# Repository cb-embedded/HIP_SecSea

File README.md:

# HIP_SecSea
Hack In Provence badge for SecSea

## Changes from V1.1 (@chris_cannes)

This version is based on the V1.1 design by @chris_cannes. The following changes were made:

**Antenna area**
- Antenna placement and copper zones reworked to comply with CC1101 datasheet requirements.
- Replaced four independent copper cutout polygons with a proper keepout zone (larger, as required by the doc).

**Layer stackup**
- Added a dedicated Ground plane (inner layer).
- Added a dedicated 3.3V Power plane (inner layer).
- Main routing moved to Top and Bottom layers.

**Power distribution**
- The 3.3V distribution tree replaced by a solid 3.3V power plane.

**GND stitching**
- Stitching vias replaced by GND vias placed as close as possible to GND pads, connecting directly into the ground plane. This ensures a controlled, low-impedance GND return path.

## TODO (before production)

- [X] Rebuild copper planes and stitching vias: add back a proper grid of stitching vias (perimeter, around RF keepout zone, under CC1101) in addition to the pad-level GND vias.
- [X] **Replace C21 and C26 — 220pF X7R on RF path**: TI reference design specifies NP0/C0G for these positions. Replace with Murata [`GRM1555C1H221JA01D`](https://www.lcsc.com/product-detail/C71693.html) (C0G, 220pF, 50V, 0402, LCSC C71693). Current part [`0402B221K500NT`](https://www.lcsc.com/product-detail/C1530.html) (FH, LCSC C1530, X7R) deviates from reference design; do not second-guess NP0 in an RF path.
- [X] **Verify crystal load capacitors C17, C18 (27pF)**: X2 specifies 15pF load. CC1101 datasheet gives Cparasitic ≈ 2.5pF typical. Effective load = 27/2 + 2.5 = 16pF — 1pF above target, acceptable. Current 27pF value is correct; no change needed unless crystal frequency trim is required.

- [ ] Use tented vias;
- [X] On ne le fait plus (trop long) ~~TODO: Changer pour antenne 868MHz (Meilleure efficacité vs petite taille de PCB), (si simple à changer).~~
- [ ] Prod entre 5 et 10.

## Production Preview JLCPCB

See [JLCPCB Pictures in this folder](KiCad_src_V1_2/production_preview)

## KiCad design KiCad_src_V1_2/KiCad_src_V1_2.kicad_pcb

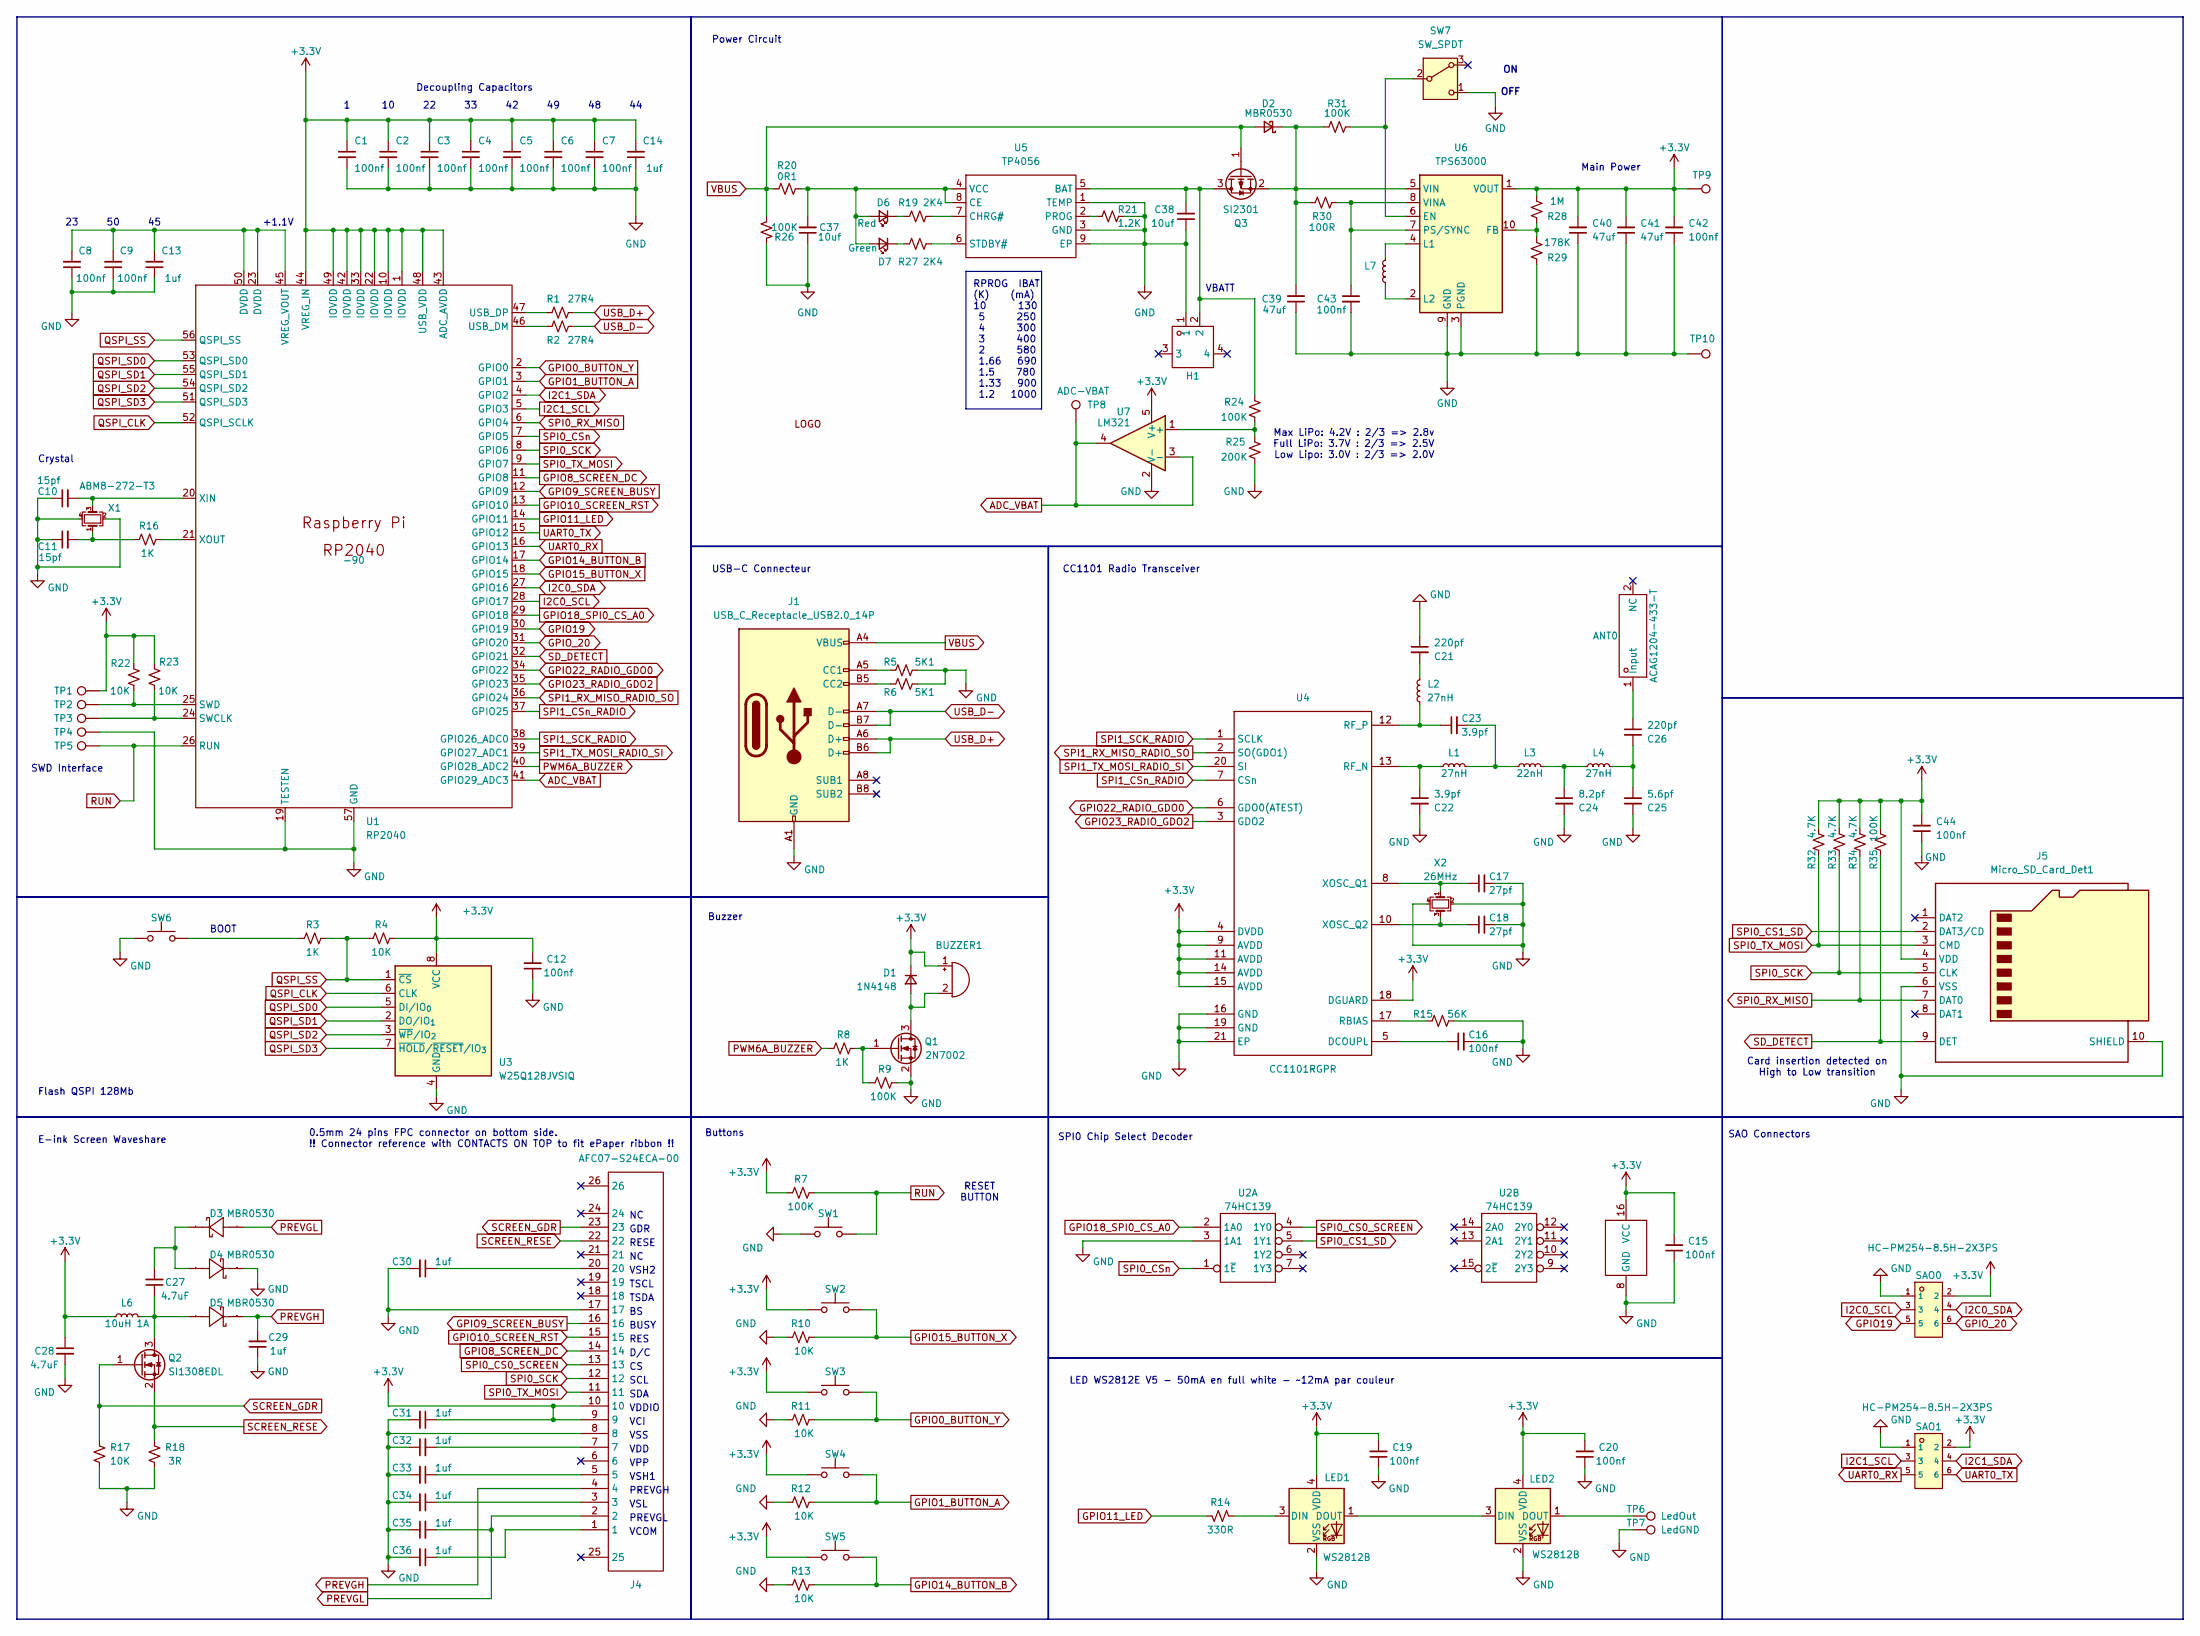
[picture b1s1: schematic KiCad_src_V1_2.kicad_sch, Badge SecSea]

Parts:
ANT0: ACAG1204-433-T; ANT-SMD_L12.0-W4.0_ACAG1204-915-T; Manufacturer Part ACAG1204-433-T; LCSC Part # C6113830
BUZZER1: MLT-8530; Buzzer MLT-8530; Manufacturer Part MLT-8530; LCSC Part # C94599
C1, C2, C3, C4, C5, C6, C7, C8, C9, C12, C15, C16, C19, C20, C42, C43, C44: 100nf; C_0402_1005Metric; Manufacturer Part CL05B104KO5NNNC; LCSC Part # C1525
C10, C11: 15pf; C_0402_1005Metric; Manufacturer Part 0402CG150J500NT; LCSC Part # C1548
C13, C14: 1uf; C_0402_1005Metric; Manufacturer Part CL05A105KA5NQNC; LCSC Part # C52923
C17, C18: 27pf; C_0402_1005Metric; Manufacturer Part 0402CG270J500NT; LCSC Part # C1557
C21, C26: 220pf; C_0402_1005Metric; Manufacturer Part 0402B221K500NT; LCSC Part # C1530
C22, C23: 3.9pf; C_0402_1005Metric; Manufacturer Part CC0402BRNPO9BN3R9; LCSC Part # C505474
C24: 8.2pf; C_0402_1005Metric; Manufacturer Part 0402CG8R2C500NT; LCSC Part # C1579
C25: 5.6pf; C_0402_1005Metric; Manufacturer Part GRM1555C1H5R6BA01D; LCSC Part # C76976
C27, C28: 4.7uF; C_0805_2012Metric; Manufacturer Part CL21A475KAQNNNE; LCSC Part # C1779
C29, C30, C31, C32, C33, C34, C35, C36: 1uf; C_0805_2012Metric; Manufacturer Part CL21B105KBFNNNE; LCSC Part # C28323
C37, C38: 10uf; C_0805_2012Metric; Manufacturer Part CL21A106KAYNNNE; LCSC Part # C15850
C39, C40, C41: 47uf; C_0805_2012Metric; Manufacturer Part CL21A476MQYNNNE; LCSC Part # C16780
D1: 1N4148; D_SOD-123; Manufacturer Part 1N4148W; LCSC Part # C81598
D2, D3, D4, D5: MBR0530; D_SOD-123; Manufacturer Part MBR0530; LCSC Part # C5204746
D6: Red; LED_0603_1608Metric; Manufacturer Part XL-1608SURC-06; LCSC Part # C965799
D7: Green; LED_0603_1608Metric; Manufacturer Part XL-1608UGC-04; LCSC Part # C965804
G1: LOGO; silkscreen_cigale
H1: WAFER-PH2.0-2PWB; CONN-SMD_2P-P2.00_XUNPU_WAFER-PH2.0-2PWB; Manufacturer Part WAFER-PH2.0-2PWB; LCSC Part # C3029440
J1: USB_C_Receptacle_USB2.0_14P; USB-C_C165948; Manufacturer Part TYPE-C-31-M-12; LCSC Part # C165948
J4: AFC07-S24ECA-00; FPC_24; Manufacturer Part AFC07-S24ECA-00; LCSC Part # C262643
J5: Micro_SD_Card_Det1; MicroSD TF-115-BCP9; Manufacturer Part XUNPU TF-115-BCP9; LCSC Part # C720505
L1, L2, L4: 27nH; L_0402_1005Metric; Manufacturer Part LQG15HS27NJ02D; LCSC Part # C12669
L3: 22nH; L_0402_1005Metric; Manufacturer Part SDCL1005C22NJTDF; LCSC Part # C15178
L6: 10uH 1A; L_Ferrocore_DLG-0403; Manufacturer Part CY43-10UH; LCSC Part # C2929419
L7: 2.2µH; L_APV_ANR4012; Manufacturer Part NR4018S2R2MT; LCSC Part # C28642347
LED1, LED2: WS2812B; LED_WS2812B-2020_PLCC4_2.0x2.0mm; Manufacturer Part WS2812B-2020; LCSC Part # C965555
Q1: 2N7002; SOT-23; Manufacturer Part 2N7002; LCSC Part # C8545
Q2: SI1308EDL; SOT-323_SC-70; Manufacturer Part SI1308EDL; LCSC Part # C7603347
Q3: SI2301; SOT-23; Manufacturer Part SI2301; LCSC Part # C2891731
R1, R2: 27R4; R_0402_1005Metric; Manufacturer Part RC-02W27R4FT; LCSC Part # C321420
R3, R8, R16: 1K; R_0402_1005Metric; Manufacturer Part 0402WGF1001TCE; LCSC Part # C11702
R4, R10, R11, R12, R13, R17, R22, R23: 10K; R_0402_1005Metric; Manufacturer Part 0402WGF1002TCE; LCSC Part # C25744
R5, R6: 5K1; R_0402_1005Metric; Manufacturer Part 0402WGF5101TCE; LCSC Part # C25905
R7, R9, R24, R26, R31, R35: 100K; R_0402_1005Metric; Manufacturer Part 0402WGF1003TCE; LCSC Part # C25741
R14: 330R; R_0402_1005Metric; Manufacturer Part 0402WGF3300TCE; LCSC Part # C25104
R15: 56K; R_0402_1005Metric; Manufacturer Part 0402WGF5602TCE; LCSC Part # C25796
R18: 3R; R_0402_1005Metric; Manufacturer Part FRC0402F3R00TS; LCSC Part # C2933093
R19, R27: 2K4; R_0402_1005Metric; Manufacturer Part 0402WGF2401TCE; LCSC Part # C25882
R20: 0R1; R_1206_3216Metric; Manufacturer Part 1206W4F100LT5E; LCSC Part # C25334
R21: 1.2K; R_0805_2012Metric_Pad1.20x1.40mm_HandSolder; Manufacturer Part 0805W8F1201T5E; LCSC Part # C17379
R25: 200K; R_0402_1005Metric; Manufacturer Part 0402WGF2003TCE; LCSC Part # C25764
R28: 1M; R_0402_1005Metric; Manufacturer Part FRC0402F1004TS; LCSC Part # C2909328
R29: 178K; R_0402_1005Metric; Manufacturer Part FRC0402F1783TS; LCSC Part # C3013156
R30: 100R; R_0402_1005Metric; Manufacturer Part FRC0402J101TS; LCSC Part # C2906884
R32, R33, R34: 4.7K; R_0402_1005Metric; Manufacturer Part FRC0402J472 TS; LCSC Part # C2906941
SAO0, SAO1: HC-PM254-8.5H-2X3PS; C22373944_HDR-SMD_6P-P2_54-V-F-R2-C3-LS7_1; LCSC C22373944
SW1, SW6: TS-1187A-B-A-B; SW_Push_1P1T_XKB_TS-1187A; Manufacturer Part TS-1187A-B-A-B; LCSC Part # C318884
SW2, SW3: K2-1112SW-A4SW-04; Manufacturer Part K2-1112SW-A4SW-04; LCSC Part # C223811
SW4, SW5: XDTD-6650; SW_Push_1P1T_NO_E-Switch_TL3301NxxxxxG; Manufacturer Part XDTD-6643-L01; LCSC Part # C7498208
SW7: SW_SPDT; SPDT SMD slide switch; Manufacturer Part SSSS811101; LCSC Part # C109335
TP1, TP2, TP3, TP4, TP5: TestPoint; TestPoint_Pad_D1.5mm
TP6: LedOut; TestPoint_Pad_D1.5mm
TP7: LedGND; TestPoint_Pad_D1.5mm
TP8, TP9, TP10: ADC-VBAT; TestPoint_Pad_D1.5mm
U1: RP2040; QFN-56-1EP_7x7mm_P0.4mm_EP3.2x3.2mm; Manufacturer Part RP2040; LCSC Part # C2040
U2: 74HC139; SOIC-16_3.9x9.9mm_P1.27mm; Manufacturer Part 74HC139D,653; LCSC Part # C5603
U3: W25Q128JVSIQ; SOIC-8_5.3x5.3mm_P1.27mm; Manufacturer Part W25Q128JVSIQ; LCSC Part # C97521
U4: CC1101RGPR; QFN-20-1EP_L4.0-W4.0-P0.5-EP2.4; Manufacturer Part CC1101RGPR; LCSC Part # C29953
U5: TP4056; ESOP-8_L4.9-W3.9-P1.27-LS6.0-BL-EP; Manufacturer Part TP4056; LCSC Part # C725790
U6: TPS63000; Texas_DRC0010J; Manufacturer Part TPS63000DRCR; LCSC Part # C24966
U7: LM321; SOT-23-5; Manufacturer Part LM321H-TR; LCSC Part # C2927688
X1: ABM8-272-T3; Crystal_SMD_Abracon_ABM8AIG-4Pin_3.2x2.5mm; Manufacturer Part ABM8-272-T3; LCSC Part # C20625731
X2: 26MHz; Crystal_SMD_3225-4Pin_3.2x2.5mm; Manufacturer Part S3226000151040; LCSC Part # C479205

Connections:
+3.3V: BUZZER1.1 (+), C1.1, C2.1, C3.1, C4.1, C5.1, C6.1, C7.1, C12.2, C14.2, C15.2, C19.2, C20.2, C28.1, C31.1, C40.2, C41.2, C42.2, C44.2, D1.1 (K), J4.9, J4.10, J5.4 (VDD), L6.1, LED1.4 (VDD), LED2.4 (VDD), R4.2, R7.1, R22.2, R23.2, R28.1, R32.2, R33.2, R34.2, R35.2, SAO0.2, SAO1.2, SW2.1, SW3.2, SW4.2, SW5.2, TP1.1 (1_1), TP9.1 (1_1), U1.1 (IOVDD), U1.10 (IOVDD), U1.22 (IOVDD), U1.33 (IOVDD), U1.42 (IOVDD), U1.43 (ADC_AVDD), U1.44 (VREG_IN), U1.48 (USB_VDD), U1.49 (IOVDD), U2.16 (VCC), U3.8 (VCC), U4.4 (DVDD), U4.9 (AVDD), U4.11 (AVDD), U4.14 (AVDD), U4.15 (AVDD), U4.18 (DGUARD), U6.1 (VOUT), U7.5 (V+)
ADC_VBAT: TP8.1 (1_1), U1.41 (GPIO29_ADC3), U7.3 (-), U7.4
GND: C1.2, C2.2, C3.2, C4.2, C5.2, C6.2, C7.2, C8.1, C9.1, C10.1, C11.1, C12.1, C13.1, C14.1, C15.1, C16.2, C17.2, C18.2, C19.1, C20.1, C21.1, C22.2, C24.2, C25.2, C28.2, C29.1, C30.2, C31.2, C32.1, C33.2, C34.2, C35.1, C36.2, C37.1, C38.1, C39.1, C40.1, C41.1, C42.1, C43.2, C44.1, D4.1 (K), H1.1, J1.A1 (GND), J1.B1 (GND), J4.8, J4.17, J5.6 (VSS), J5.10 (SHIELD), LED1.2 (VSS), LED2.2 (VSS), Q1.2 (S), R5.1, R6.2, R9.2, R10.1, R11.1, R12.1, R13.1, R15.2, R17.1, R18.1, R21.1, R25.1, R26.2, R29.2, SAO0.1, SAO1.1, SW1.1, SW6.1, SW7.1 (C), TP4.1 (1_1), TP7.1 (1_1), TP10.1 (1_1), U1.19 (TESTEN), U1.57 (GND), U2.3 (1A1), U2.8 (GND), U3.4 (GND), U4.16 (GND), U4.19 (GND), U4.21 (EP), U5.1 (TEMP), U5.3 (GND), U5.9 (EP), U6.3 (PGND), U6.9 (GND), U6.11 (PGND), U7.2 (V-), X1.2, X1.4, X2.2, X2.4
GPIO0_BUTTON_Y: R11.2, SW3.1, U1.2 (GPIO0)
GPIO1_BUTTON_A: R12.2, SW4.1, U1.3 (GPIO1)
GPIO8_SCREEN_DC: J4.14, U1.11 (GPIO8)
GPIO9_SCREEN_BUSY: J4.16, U1.12 (GPIO9)
GPIO10_SCREEN_RST: J4.15, U1.13 (GPIO10)
GPIO11_LED: R14.1, U1.14 (GPIO11)
GPIO14_BUTTON_B: R13.2, SW5.1, U1.17 (GPIO14)
GPIO15_BUTTON_X: R10.2, SW2.2, U1.18 (GPIO15)
GPIO18_SPI0_CS_A0: U1.29 (GPIO18), U2.2 (1A0)
GPIO19: SAO0.5, U1.30 (GPIO19)
GPIO22_RADIO_GDO0: U1.34 (GPIO22), U4.6 (GDO0(ATEST))
GPIO23_RADIO_GDO2: U1.35 (GPIO23), U4.3 (GDO2)
GPIO_20: SAO0.6, U1.31 (GPIO20)
I2C0_SCL: SAO0.3, U1.28 (GPIO17)
I2C0_SDA: SAO0.4, U1.27 (GPIO16)
I2C1_SCL: SAO1.3, U1.5 (GPIO3)
I2C1_SDA: SAO1.4, U1.4 (GPIO2)
unnamed: ANT0.1 (Input_1), C26.1
unnamed: BUZZER1.2 (-), D1.2 (A), Q1.3 (D)
unnamed: C11.2, R16.1, X1.1
unnamed: C21.2, L2.2
unnamed: C23.2, L1.2, L3.1
unnamed: C24.1, L3.2, L4.1
unnamed: C25.1, C26.2, L4.2
unnamed: C30.1, J4.20
unnamed: C32.2, J4.7
unnamed: C33.1, J4.5
unnamed: C34.1, J4.3
unnamed: C36.1, J4.1
unnamed: C39.2, D2.1 (K), Q3.2 (S), R30.2, R31.1, U6.5 (VIN)
unnamed: C27.2, D3.1 (K), D4.2 (A)
unnamed: C27.1, D5.2 (A), L6.2, Q2.3 (D)
unnamed: C37.2, D6.2 (A), D7.2 (A), R20.1, U5.4 (VCC), U5.8 (CE)
unnamed: D6.1 (K), R19.2
unnamed: D7.1 (K), R27.2
unnamed: J1.A5 (CC1), R5.2
unnamed: J1.B5 (CC2), R6.1
unnamed: LED1.3 (DIN), R14.2
unnamed: LED1.1 (DOUT), LED2.3 (DIN)
unnamed: LED2.1 (DOUT), TP6.1 (1_1)
unnamed: Q1.1 (G), R8.2, R9.1
unnamed: C38.2, H1.2, Q3.3 (D), R24.2, U5.5 (BAT)
unnamed: R3.2, SW6.2
unnamed: R31.2, SW7.2 (B), U6.6 (EN)
unnamed: R23.1, TP3.1 (1_1), U1.24 (SWCLK)
unnamed: R22.1, TP2.1 (1_1), U1.25 (SWD)
unnamed: R2.1, U1.46 (USB_DM)
unnamed: R1.2, U1.47 (USB_DP)
unnamed: C8.2, C9.2, C13.2, U1.23 (DVDD), U1.45 (VREG_VOUT), U1.50 (DVDD)
unnamed: C10.2, U1.20 (XIN), X1.3
unnamed: R16.2, U1.21 (XOUT)
unnamed: C16.1, U4.5 (DCOUPL)
unnamed: R15.1, U4.17 (RBIAS)
unnamed: C22.1, L1.1, U4.13 (RF_N)
unnamed: C23.1, L2.1, U4.12 (RF_P)
unnamed: C17.1, U4.8 (XOSC_Q1), X2.1
unnamed: C18.1, U4.10 (XOSC_Q2), X2.3
unnamed: R19.1, U5.7 (CHRG#)
unnamed: R21.2, U5.2 (PROG)
unnamed: R27.1, U5.6 (STDBY#)
unnamed: R28.2, R29.1, U6.10 (FB)
unnamed: L7.2, U6.4 (L1)
unnamed: L7.1, U6.2 (L2)
unnamed: C43.1, R30.1, U6.7 (PS/SYNC), U6.8 (VINA)
unnamed: R24.1, R25.2, U7.1 (+)
PREVGH: C29.2, D5.1 (K), J4.4
PREVGL: C35.2, D3.2 (A), J4.2
PWM6A_BUZZER: R8.1, U1.40 (GPIO28_ADC2)
QSPI_CLK: U1.52 (QSPI_SCLK), U3.6 (CLK)
QSPI_SD0: U1.53 (QSPI_SD0), U3.5 (DI/IO_{0})
QSPI_SD1: U1.55 (QSPI_SD1), U3.2 (DO/IO_{1})
QSPI_SD2: U1.54 (QSPI_SD2), U3.3 (~WP/IO_{2})
QSPI_SD3: U1.51 (QSPI_SD3), U3.7 (~HOLD/~RESET/IO_{3})
QSPI_SS: R3.1, R4.1, U1.56 (QSPI_SS), U3.1 (~CS)
RUN: R7.2, SW1.2, TP5.1 (1_1), U1.26 (RUN)
SCREEN_GDR: J4.23, Q2.1 (G), R17.2
SCREEN_RESE: J4.22, Q2.2 (S), R18.2
SD_DETECT: J5.9 (DET), R35.1, U1.32 (GPIO21)
SPI0_CS0_SCREEN: J4.13, U2.4 (1Y0)
SPI0_CS1_SD: J5.2 (DAT3/CD), U2.5 (1Y1)
SPI0_CSn: U1.7 (GPIO5), U2.1 (1~E)
SPI0_RX_MISO: J5.7 (DAT0), R34.1, U1.6 (GPIO4)
SPI0_SCK: J4.12, J5.5 (CLK), R33.1, U1.8 (GPIO6)
SPI0_TX_MOSI: J4.11, J5.3 (CMD), R32.1, U1.9 (GPIO7)
SPI1_CSn_RADIO: U1.37 (GPIO25), U4.7 (CSn)
SPI1_RX_MISO_RADIO_SO: U1.36 (GPIO24), U4.2 (SO(GDO1))
SPI1_SCK_RADIO: U1.38 (GPIO26_ADC0), U4.1 (SCLK)
SPI1_TX_MOSI_RADIO_SI: U1.39 (GPIO27_ADC1), U4.20 (SI)
UART0_RX: SAO1.5, U1.16 (GPIO13)
UART0_TX: SAO1.6, U1.15 (GPIO12)
USB_D+: J1.A6 (D+), J1.B6 (D+), R1.1
USB_D-: J1.A7 (D-), J1.B7 (D-), R2.2
VBUS: D2.2 (A), J1.A4 (VBUS), J1.B4 (VBUS), Q3.1 (G), R20.2, R26.1

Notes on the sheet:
VDD
VDDIO
E-ink Screen Waveshare
Main Power
RPROG IBAT (K) (mA) 10 130 5 250 4 300 3 400 2 580 1.66 690 1.5 780 1.33 900 1.2 1000
SAO Connectors
VSH1
VPP
TSCL
Flash QSPI 128Mb
VCOM
PREVGH
SDA
VSH2
Max LiPo: 4.2V : 2/3 => 2.8v Full LiPo: 3.7V : 2/3 => 2.5V Low Lipo: 3.0V : 2/3 => 2.0V
Buzzer
ON OFF
+1.1V
RES
GDR
Buttons
D/C
CC1101 Radio Transceiver
Card insertion detected on High to Low transition
VCI
BUSY
Crystal
Decoupling Capacitors
PREVGL
SPI0 Chip Select Decoder
LED WS2812E V5 - 50mA en full white - ~12mA par couleur
VSS
VSL
SCL
RESET BUTTON
VBATT
SWD Interface
Power Circuit
RESE
TSDA

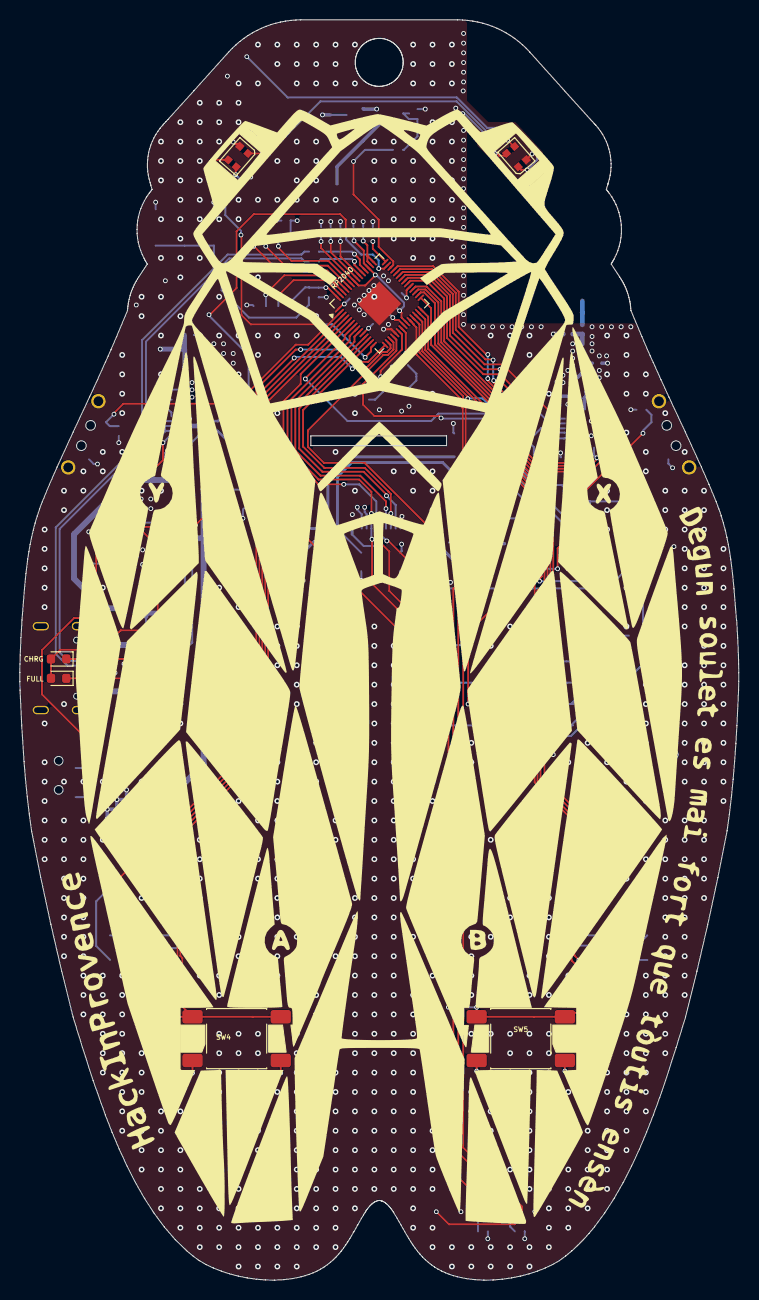
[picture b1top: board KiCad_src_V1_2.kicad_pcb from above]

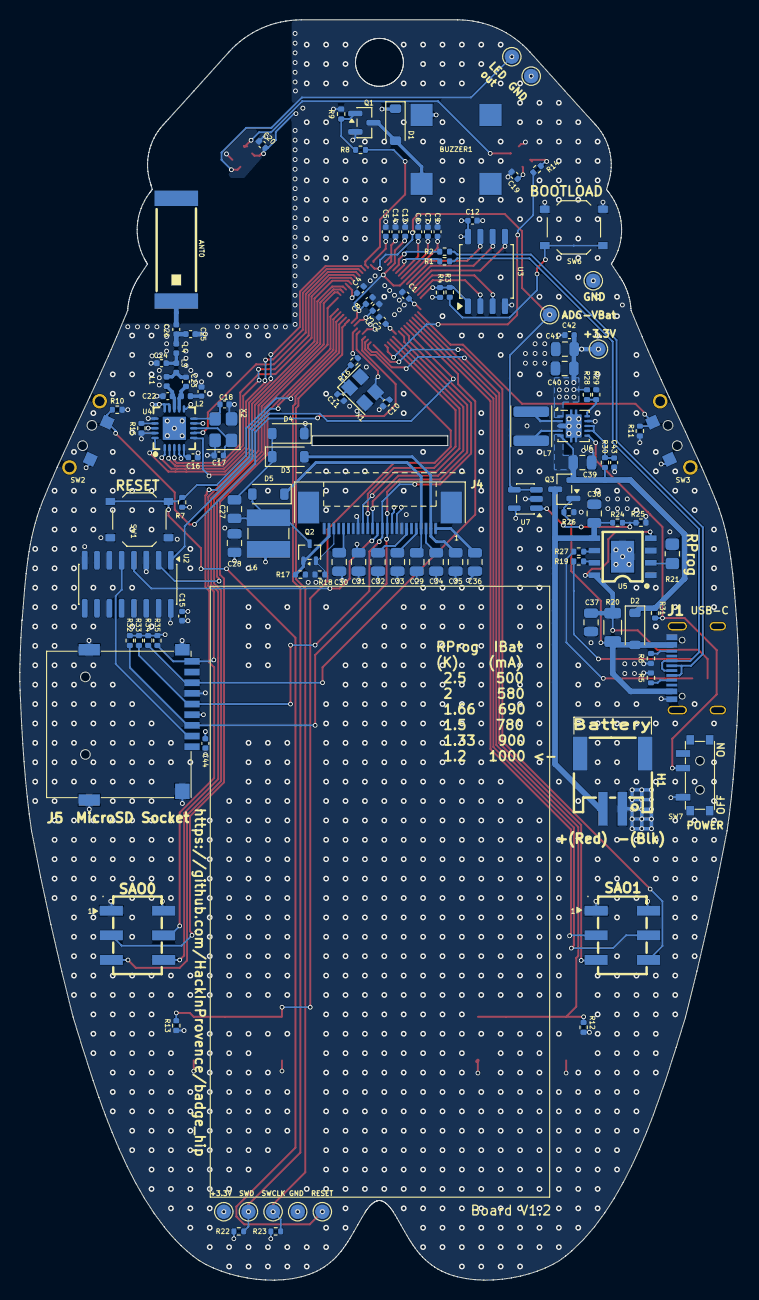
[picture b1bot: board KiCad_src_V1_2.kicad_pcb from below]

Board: 4 copper layers, 74.1 x 130.0 mm, 132 parts (124 on the bottom side), 96 nets.

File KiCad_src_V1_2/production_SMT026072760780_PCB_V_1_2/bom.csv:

Designator,Footprint,Quantity,Value,LCSC Part #
ANT0,ANT-SMD_L12.0-W4.0_ACAG1204-915-T,1,ACAG1204-433-T,C6113830
BUZZER1,Buzzer MLT-8530,1,MLT-8530,C94599
"C1, C12, C15, C16, C19, C2, C20, C3, C4, C42, C43, C44, C5, C6, C7, C8, C9",0402,17,100nf,C1525
"C10, C11",0402,2,15pf,C1548
"C13, C14",0402,2,1uf,C52923
"C17, C18",0402,2,27pf,C1557
"C21, C26",0402,2,220pf,C1530
"C22, C23",0402,2,3.9pf,C505474
C24,0402,1,8.2pf,C1579
C25,0402,1,5.6pf,C76976
"C27, C28",0805,2,4.7uF,C1779
"C29, C30, C31, C32, C33, C34, C35, C36",0805,8,1uf,C28323
"C37, C38",0805,2,10uf,C15850
"C39, C40, C41",0805,3,47uf,C16780
D1,D_SOD-123,1,1N4148,C81598
"D2, D3, D4, D5",D_SOD-123,4,MBR0530,C5204746
D6,0603,1,Red,C965799
D7,0603,1,Green,C965804
H1,CONN-SMD_2P-P2.00_XUNPU_WAFER-PH2.0-2PWB,1,WAFER-PH2.0-2PWB,C3029440
J1,USB-C_C165948,1,USB_C_Receptacle_USB2.0_14P,C165948
J4,FPC_24,1,AFC07-S24ECA-00,C262643
J5,MicroSD TF-115-BCP9,1,Micro_SD_Card_Det1,C720505
"L1, L2, L4",0402,3,27nH,C12669
L3,0402,1,22nH,C15178
L6,L_Ferrocore_DLG-0403,1,10uH 1A,C2929419
L7,L_APV_ANR4012,1,2.2µH,C28642347
"LED1, LED2",LED_WS2812B-2020_PLCC4_2.0x2.0mm,2,WS2812B,C965555
Q1,SOT-23,1,2N7002,C8545
Q2,SOT-323_SC-70,1,SI1308EDL,C7603347
Q3,SOT-23,1,SI2301,C2891731
"R1, R2",0402,2,27R4,C321420
"R10, R11, R12, R13, R17, R22, R23, R4",0402,8,10K,C25744
R14,0402,1,330R,C25104
R15,0402,1,56K,C25796
"R16, R3, R8",0402,3,1K,C11702
R18,0402,1,3R,C2933093
"R19, R27",0402,2,2K4,C25882
R20,1206,1,0R1,C25334
R21,0805,1,1.2K,C17379
"R24, R26, R31, R35, R7, R9",0402,6,100K,C25741
R25,0402,1,200K,C25764
R28,0402,1,1M,C2909328
R29,0402,1,178K,C3013156
R30,0402,1,100R,C2906884
"R32, R33, R34",0402,3,4.7K,C2906941
"R5, R6",0402,2,5K1,C25905
"SAO0, SAO1",C22373944_HDR-SMD_6P-P2_54-V-F-R2-C3-LS7_1,2,HC-PM254-8.5H-2X3PS,C22373944
"SW1, SW6",SW_Push_1P1T_XKB_TS-1187A,2,TS-1187A-B-A-B,C318884
"SW2, SW3",K2-1112SW-A4SW-04,2,K2-1112SW-A4SW-04,C223811
"SW4, SW5",SW_Push_1P1T_NO_E-Switch_TL3301NxxxxxG,2,XDTD-6650,C7498208
SW7,SPDT SMD slide switch,1,SW_SPDT,C109335
U1,QFN-56-1EP_7x7mm_P0.4mm_EP3.2x3.2mm,1,RP2040,C2040
U2,SOIC-16_3.9x9.9mm_P1.27mm,1,74HC139,C5603
U3,SOIC-8_5.3x5.3mm_P1.27mm,1,W25Q128JVSIQ,C97521
U4,QFN-20-1EP_L4.0-W4.0-P0.5-EP2.4,1,CC1101RGPR,C29953
U5,ESOP-8_L4.9-W3.9-P1.27-LS6.0-BL-EP,1,TP4056,C725790
U6,Texas_DRC0010J,1,TPS63000,C24966
U7,SOT-23-5,1,LM321,C2927688
X1,Crystal_SMD_Abracon_ABM8AIG-4Pin_3.2x2.5mm,1,ABM8-272-T3,C20625731
X2,Crystal_SMD_3225-4Pin_3.2x2.5mm,1,26MHz,C479205

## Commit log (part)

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2026-01-14 Add README with project title and description
2026-01-14 Files import
2026-01-14 Add files via upload
    file up to date
2026-06-29 Consumption fix: Op amp now connected to +3.3V instead of VBat (Schematic + PCB)
2026-06-29 Working on new antenna keepout zone and position.
2026-06-29 SAO connector added (with 3D). WIP on the antenna.
2026-06-29 WIP routing
2026-06-29 WIP Routing....
